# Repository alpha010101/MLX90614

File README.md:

赤外線非接触温度センサー（MLX90614)を筐体に実装するための補助基板

SchematicとPCB-LayoutをAutodesk-Eagle無償版で作成し、elecrowで製造することを前提にガーバーを作成

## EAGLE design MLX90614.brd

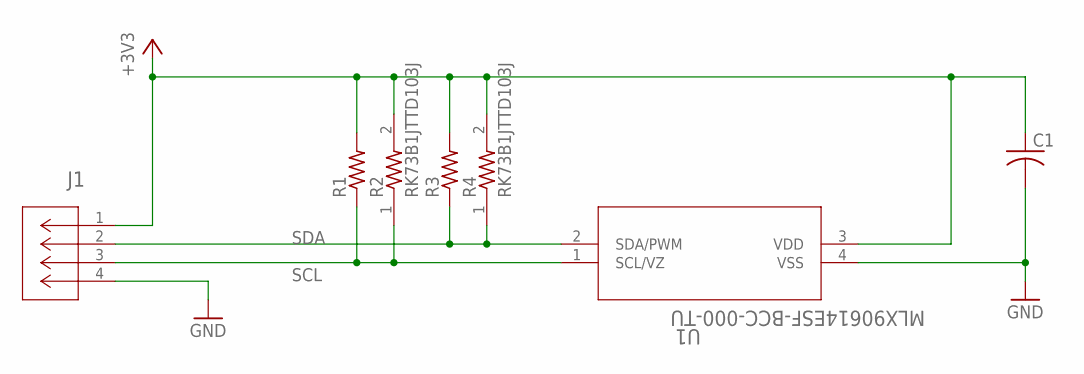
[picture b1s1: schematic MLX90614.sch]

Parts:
C1: C-US025-024X044; C025-024X044
J1: S4B-PH-K-S(LF)(SN); CONN_S4B-PH-K-S_JST
R1, R3: R-US_0204/7; 0204/7
R2, R4: RK73B1JTTD103J; RESC1608X55N
U1: MLX90614ESF-BCC-000-TU; MLX90614XCC_MEL

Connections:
+3V3: C1.1, J1.1, R1.2, R2.2, R3.2, R4.2, U1.3 (VDD)
GND: C1.2, J1.4, U1.4 (VSS)
SCL: J1.3, R1.1, R2.1, U1.1 (SCL/VZ)
SDA: J1.2, R3.1, R4.1, U1.2 (SDA/PWM)

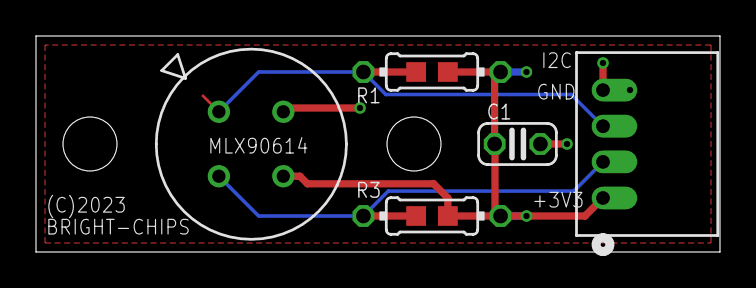
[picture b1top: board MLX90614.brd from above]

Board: 2 copper layers, 38.0 x 12.0 mm, 7 parts (0 on the bottom side), 4 nets.

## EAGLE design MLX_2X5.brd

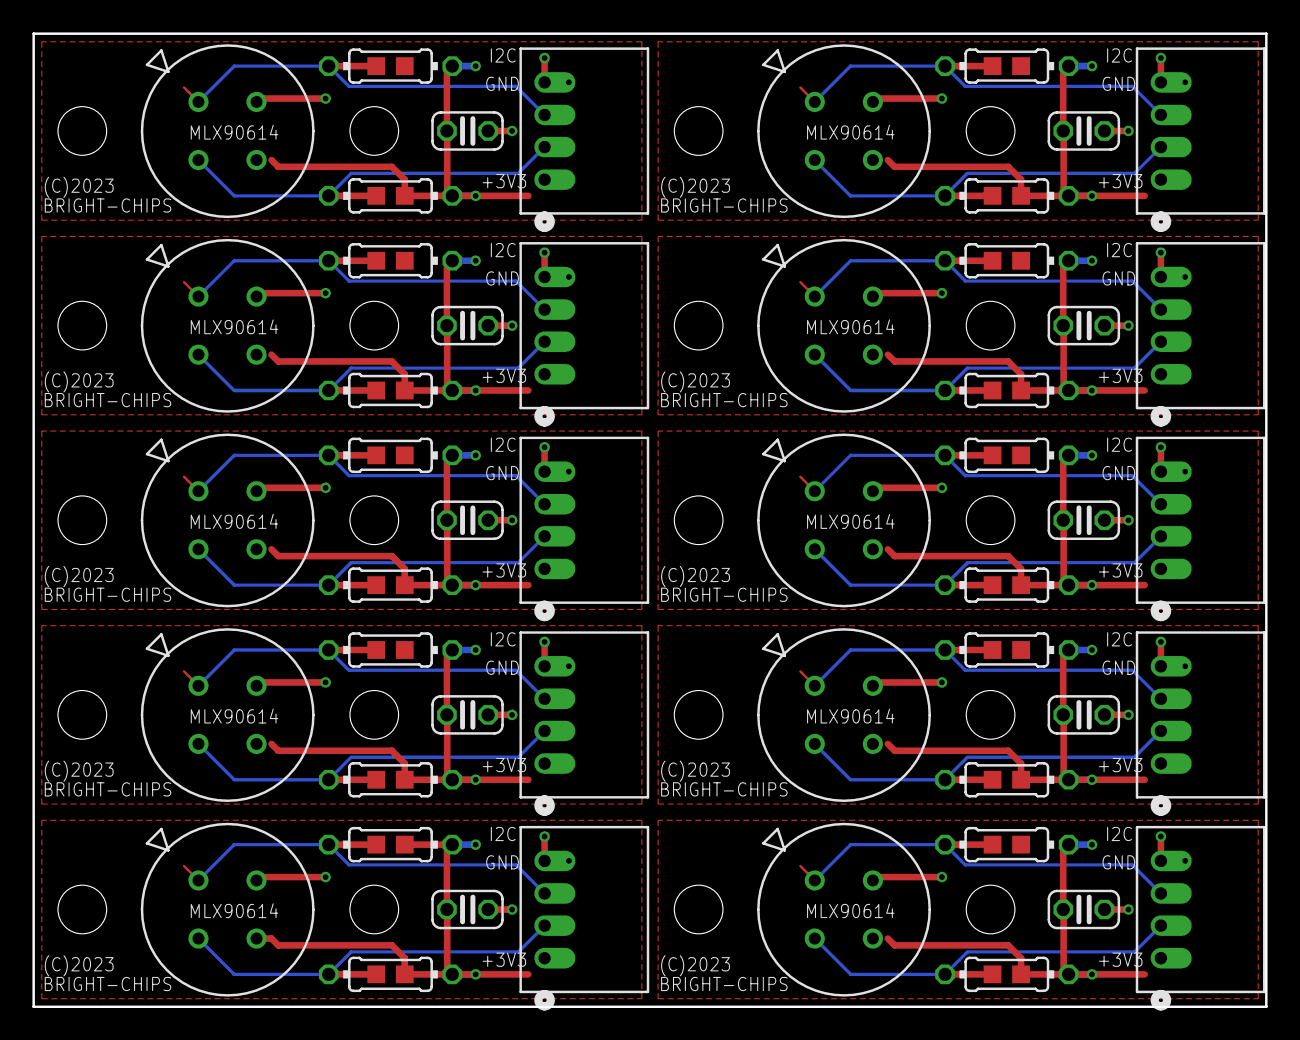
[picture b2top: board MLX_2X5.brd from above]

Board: 2 copper layers, 76.0 x 60.0 mm, 70 parts (0 on the bottom side), 40 nets.

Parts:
C1, C2, C3, C4, C5, C6, C7, C8, C9, C10: C025-024X044
J1, J2, J3, J4, J5, J6, J7, J8, J9, J10: S4B-PH-K-S(LF)(SN); CONN_S4B-PH-K-S_JST
R1, R3, R5, R7, R9, R11, R13, R15, R17, R19, R21, R23, R25, R27, R29, R31, R33, R35, R37, R39: 0204/7
R2, R4, R6, R8, R10, R12, R14, R16, R18, R20, R22, R24, R26, R28, R30, R32, R34, R36, R38, R40: RK73B1JTTD103J; RESC1608X55N
U1, U2, U3, U4, U5, U6, U7, U8, U9, U10: MLX90614ESF-BCC-000-TU; MLX90614XCC_MEL

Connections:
+3V1: C2.1, J2.1, R5.2, R6.2, R7.2, R8.2, U2.3
+3V2: C3.1, J3.1, R9.2, R10.2, R11.2, R12.2, U3.3
+3V3: C1.1, J1.1, R1.2, R2.2, R3.2, R4.2, U1.3
+3V4: C4.1, J4.1, R13.2, R14.2, R15.2, R16.2, U4.3
+3V5: C5.1, J5.1, R17.2, R18.2, R19.2, R20.2, U5.3
+3V6: C6.1, J6.1, R21.2, R22.2, R23.2, R24.2, U6.3
+3V7: C7.1, J7.1, R25.2, R26.2, R27.2, R28.2, U7.3
+3V8: C8.1, J8.1, R29.2, R30.2, R31.2, R32.2, U8.3
+3V9: C9.1, J9.1, R33.2, R34.2, R35.2, R36.2, U9.3
+3V10: C10.1, J10.1, R37.2, R38.2, R39.2, R40.2, U10.3
GND: C1.2, J1.4, U1.4
GND1: C2.2, J2.4, U2.4
GND2: C3.2, J3.4, U3.4
GND3: C4.2, J4.4, U4.4
GND4: C5.2, J5.4, U5.4
GND5: C6.2, J6.4, U6.4
GND6: C7.2, J7.4, U7.4
GND7: C8.2, J8.4, U8.4
GND8: C9.2, J9.4, U9.4
GND9: C10.2, J10.4, U10.4
SCL: J1.3, R1.1, R2.1, U1.1
SCL1: J2.3, R5.1, R6.1, U2.1
SCL2: J3.3, R9.1, R10.1, U3.1
SCL3: J4.3, R13.1, R14.1, U4.1
SCL4: J5.3, R17.1, R18.1, U5.1
SCL5: J6.3, R21.1, R22.1, U6.1
SCL6: J7.3, R25.1, R26.1, U7.1
SCL7: J8.3, R29.1, R30.1, U8.1
SCL8: J9.3, R33.1, R34.1, U9.1
SCL9: J10.3, R37.1, R38.1, U10.1
SDA: J1.2, R3.1, R4.1, U1.2
SDA1: J2.2, R7.1, R8.1, U2.2
SDA2: J3.2, R11.1, R12.1, U3.2
SDA3: J4.2, R15.1, R16.1, U4.2
SDA4: J5.2, R19.1, R20.1, U5.2
SDA5: J6.2, R23.1, R24.1, U6.2
SDA6: J7.2, R27.1, R28.1, U7.2
SDA7: J8.2, R31.1, R32.1, U8.2
SDA8: J9.2, R35.1, R36.1, U9.2
SDA9: J10.2, R39.1, R40.1, U10.2

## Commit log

2025-01-01 initial release

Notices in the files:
MLX90614.brd:
(C)2023
parts and their libraries:
COPYRIGHT: Copyright (C) 2023 Ultra Librarian. All rights reserved.
